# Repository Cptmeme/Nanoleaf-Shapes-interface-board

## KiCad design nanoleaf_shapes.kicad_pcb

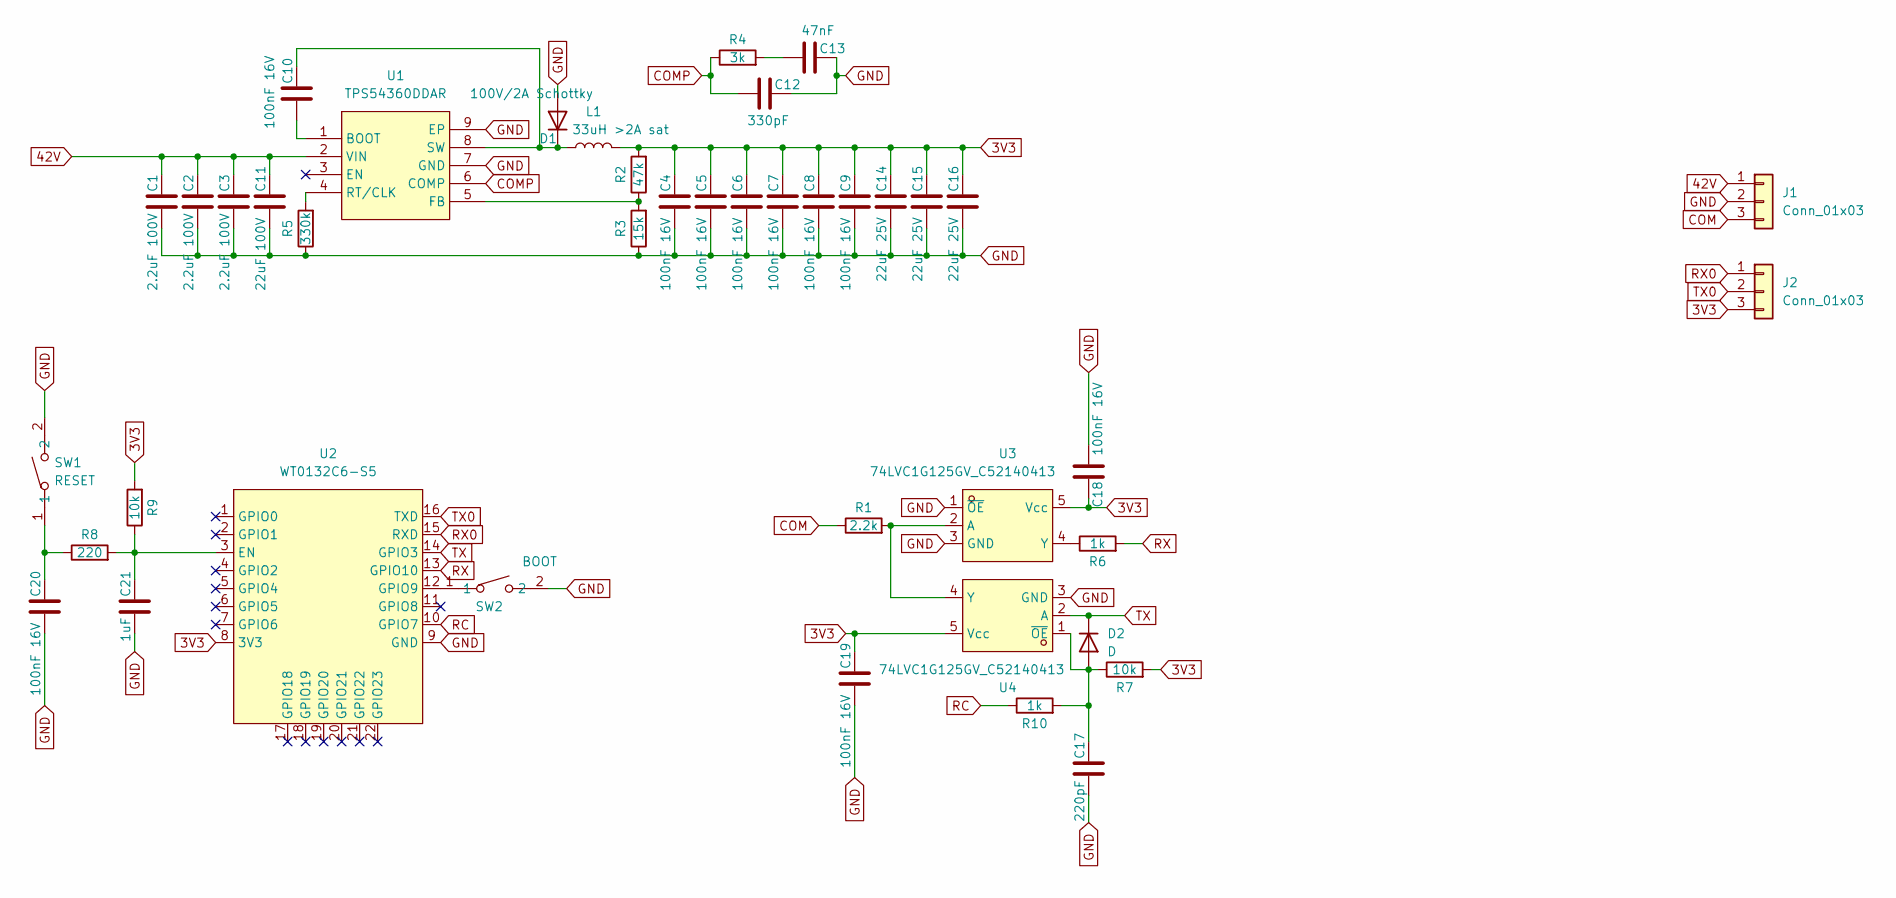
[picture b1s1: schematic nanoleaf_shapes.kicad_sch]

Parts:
C1, C2, C3: 2.2uF 100V; C1210; JLCPCB C5449052
C4, C5, C6, C7, C8, C9, C10, C18, C19, C20: 100nF 16V; C0402; JLCPCB C1525
C11: 22uF 100V; CAP-SMD_BD6.3-L6.6-W6.6-FD-1; JLCPCB C47023097
C12: 330pF; C0603; JLCPCB C1664
C13: 47nF; C0603; JLCPCB C1622
C14, C15, C16: 22uF 25V; C0805; JLCPCB C45783
C17: 220pF; C0402; JLCPCB C1530
C21: 1uF; C0402; JLCPCB C52923
D1: 100V/2A Schottky; SMA_L4.3-W2.6-LS5.2-RD; JLCPCB C14996
D2: D; D_SOD-123; JLCPCB C81598
J1, J2: Conn_01x03; PinHeader_1x03_P2.54mm_Vertical
L1: 33uH >2A sat; IND-SMD_L5.2-W5.2_YSPI0530; JLCPCB C20417191
R1: 2.2k; R0402; JLCPCB C25879
R2: 47k; R0402; JLCPCB C25792
R3: 15k; R0402; JLCPCB C25756
R4: 3k; R0603; JLCPCB C4211
R5: 330k; R0603; JLCPCB C23137
R6, R10: 1k; R0402; JLCPCB C11702
R7, R9: 10k; R0402; JLCPCB C25744
R8: 220; R0402; JLCPCB C25091
SW1: RESET; SW-SMD_L3.9-W3.0-P4.45; MPN TS-1088-AR02016; LCSC Part C720477
SW2: BOOT; SW-SMD_L3.9-W3.0-P4.45; MPN TS-1088-AR02016; LCSC Part C720477
U1: TPS54360DDAR; SOIC-8_L5.0-W4.0-P1.27-LS6.0-BL-EP2.0; MPN TPS54360DDAR; LCSC Part C44377
U2: WT0132C6-S5; LCSC Part C9900241604
U3, U4: 74LVC1G125GV_C52140413; SOT-23-5_L3.0-W1.7-P0.95-LS2.8-BR; MPN 74LVC1G125GV; LCSC Part C52140413

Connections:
3V3: C4.1, C5.1, C6.1, C7.1, C8.1, C9.1, C14.1, C15.1, C16.1, C18.1, C19.1, J2.3, L1.2, R2.2, R7.2, R9.2, U2.8 (3V3), U3.5 (Vcc), U4.5 (Vcc)
42V: C1.1, C2.1, C3.1, C11.1, J1.1, U1.2 (VIN)
COM: J1.3, R1.1
COMP: C12.2, R4.1, U1.6 (COMP)
GND: C1.2, C2.2, C3.2, C4.2, C5.2, C6.2, C7.2, C8.2, C9.2, C11.2, C12.1, C13.1, C14.2, C15.2, C16.2, C17.2, C18.2, C19.2, C20.2, C21.2, D1.2 (A), J1.2, R3.1, R5.1, SW1.2, SW2.2, U1.7 (GND), U1.9 (EP), U2.9 (GND), U3.1 (~OE), U3.3 (GND), U4.3 (GND)
unnamed: C13.2, R4.2
unnamed: C20.1, R8.1, SW1.1
unnamed: C10.1, D1.1 (K), L1.1, U1.8 (SW)
unnamed: C17.1, D2.2 (A), R7.1, R10.2, U4.1 (~OE)
unnamed: C10.2, U1.1 (BOOT)
unnamed: R2.1, R3.2, U1.5 (FB)
unnamed: R5.2, U1.4 (RT/CLK)
unnamed: C21.1, R8.2, R9.1, U2.3 (EN)
unnamed: SW2.1, U2.12 (GPIO9)
unnamed: R1.2, U3.2 (A), U4.4 (Y)
unnamed: R6.1, U3.4 (Y)
RC: R10.1, U2.10 (GPIO7)
RX: R6.2, U2.13 (GPIO10)
RX0: J2.1, U2.15 (RXD)
TX: D2.1 (K), U2.14 (GPIO3), U4.2 (A)
TX0: J2.2, U2.16 (TXD)

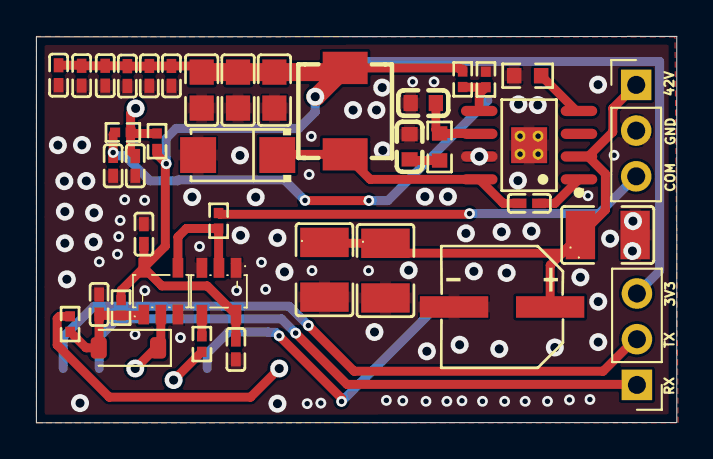
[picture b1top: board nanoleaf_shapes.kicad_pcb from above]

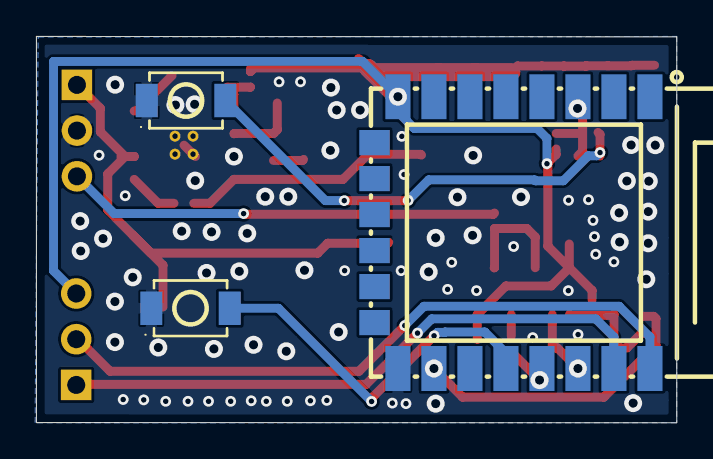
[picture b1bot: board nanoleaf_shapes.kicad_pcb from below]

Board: 2 copper layers, 35.6 x 21.5 mm, 42 parts (3 on the bottom side), 21 nets.
